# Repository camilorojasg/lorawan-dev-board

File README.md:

# lorawan-dev-board
Schematics and documentation of my Arduino LoRaWAN development board

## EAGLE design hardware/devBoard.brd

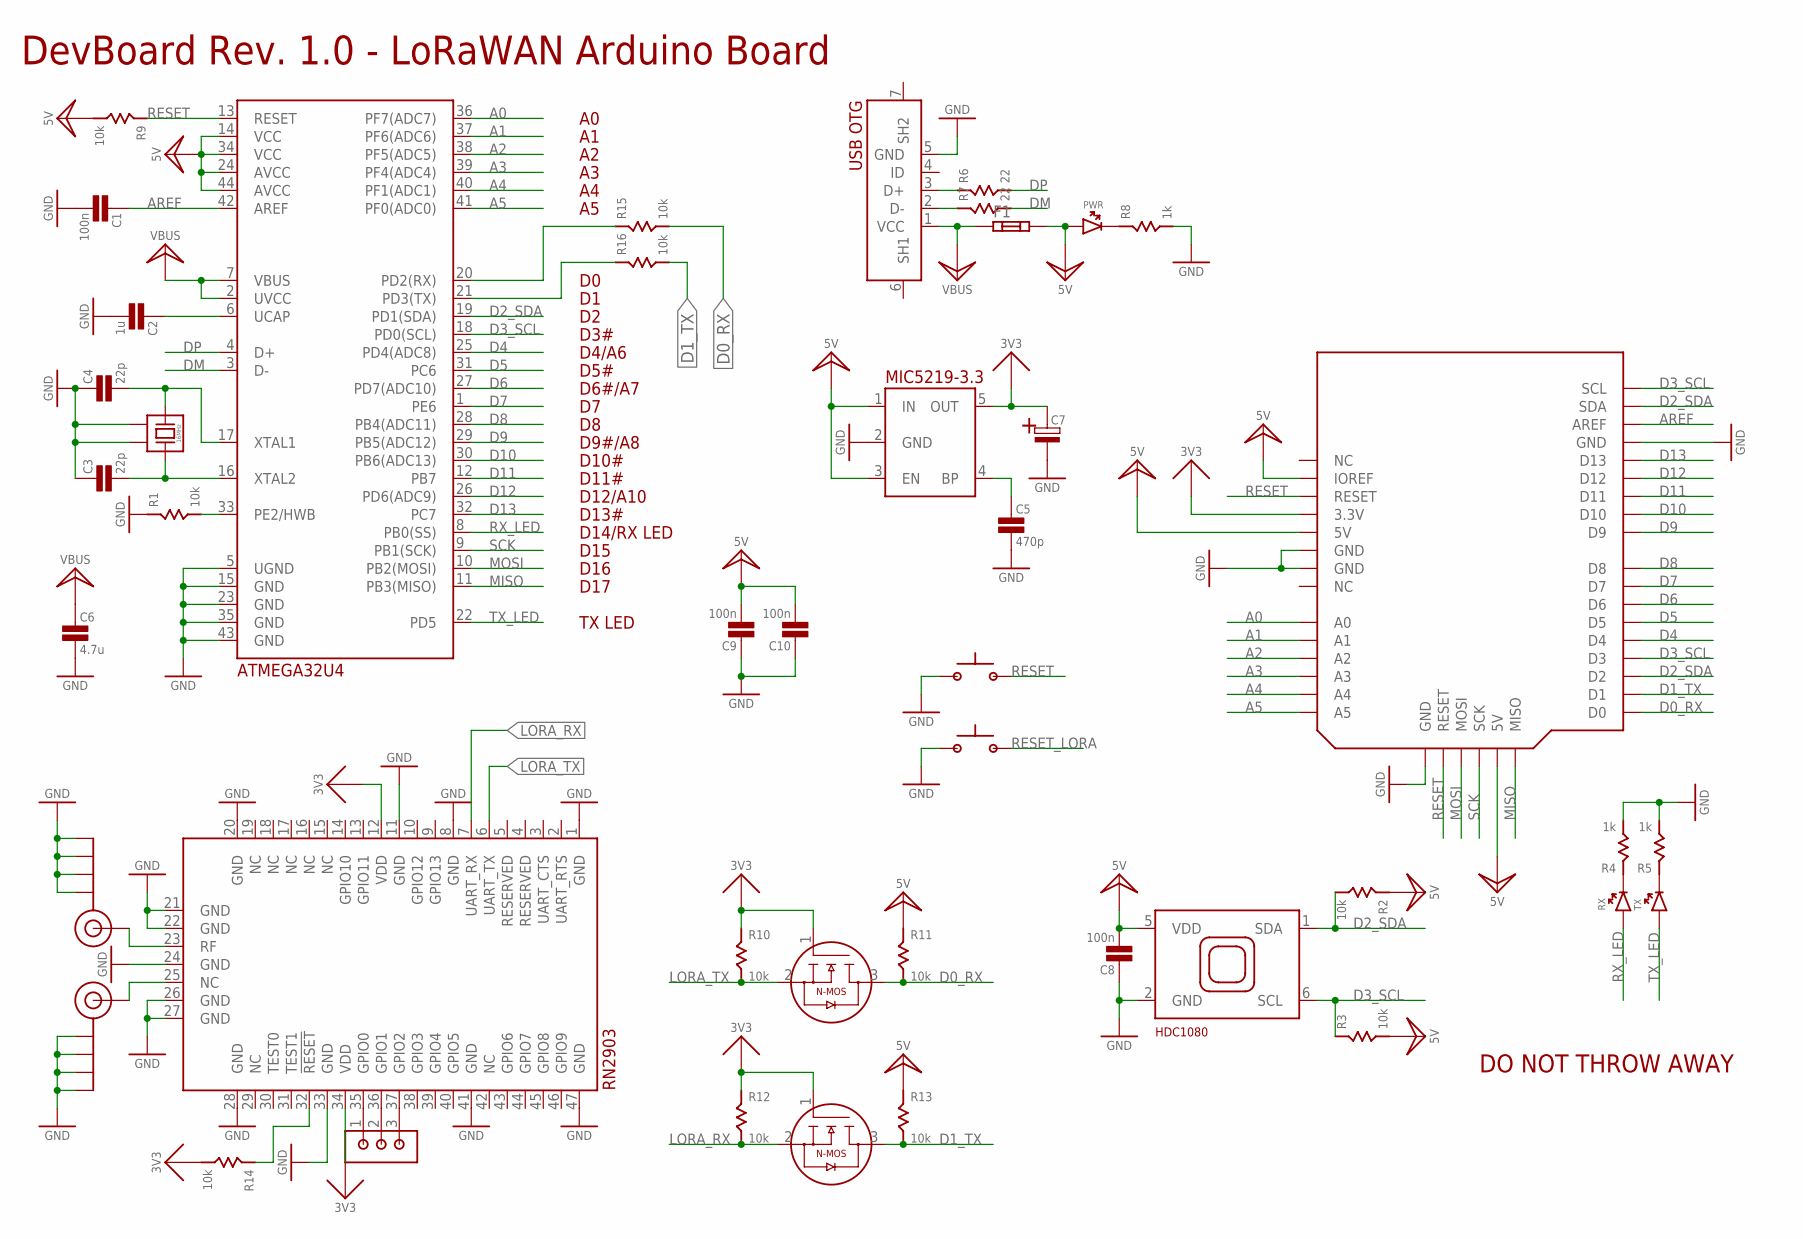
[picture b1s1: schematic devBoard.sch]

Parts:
C1, C8, C9, C10: 100n; 0603
C2: 1u; 0603
C3, C4: 22p; 0603
C5: 470p; 0603
C6: 4.7u; 0603
C7: CT3216
F1: MF-MSMF050
J$1, J$2: SMA_EDGE; SMA-EDGE
PWR: PWR; 0603LED
R1, R2, R3, R9, R10, R11, R12, R13, R14, R15, R16: 10k; 0603
R4, R5, R8: 1k; 0603
R6, R7: 22; 0603
RX: RX; 0603LED
SW2, SW3: PUSH_BTN
T1, T2: BSS138; SOT23-3
TX: TX; 0603LED
U1: RN2903
U$1: ATMEGA32U4-MU; QFN44
U$2: ARDUINO_UNO
U$9: HDC1080
U$34: MIC5219-3.3; SOT-23-5
U$45: USB_OTG
U$59: 1X3_HEADER
U$65: DONT_THROW
Y1: 16MHz; XTAL3225

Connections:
3V3: C7.AN, R10.1, R12.1, R14.2, T1.1 (G), T2.1 (G), U1.12 (VDD), U1.34 (VDD), U$2.3.3V, U$34.5 (OUT)
5V: C8.2, C9.2, C10.2, F1.2, PWR.AN, R2.1, R3.2, R9.2, R11.1, R13.1, U$1.14 (VCC), U$1.24 (AVCC), U$1.34 (VCC), U$1.44 (AVCC), U$2.5V, U$2.ICSP_2 (5V), U$2.IOREF, U$9.5 (VDD), U$34.1 (IN), U$34.3 (EN)
A0: U$1.36 (PF7(ADC7)), U$2.A0
A1: U$1.37 (PF6(ADC6)), U$2.A1
A2: U$1.38 (PF5(ADC5)), U$2.A2
A3: U$1.39 (PF4(ADC4)), U$2.A3
A4: U$1.40 (PF1(ADC1)), U$2.A4
A5: U$1.41 (PF0(ADC0)), U$2.A5
AREF: C1.1, U$1.42 (AREF), U$2.AREF
D0_RX: R11.2, R15.2, T1.3 (D), U$2.D0
D1_TX: R13.2, R16.2, T2.3 (D), U$2.D1
D2_SDA: R2.2, U$1.19 (PD1(SDA)), U$2.D2, U$2.SDA, U$9.1 (SDA)
D3_SCL: R3.1, U$1.18 (PD0(SCL)), U$2.D3, U$2.SCL, U$9.6 (SCL)
D4: U$1.25 (PD4(ADC8)), U$2.D4
D5: U$1.31 (PC6), U$2.D5
D6: U$1.27 (PD7(ADC10)), U$2.D6
D7: U$1.1 (PE6), U$2.D7
D8: U$1.28 (PB4(ADC11)), U$2.D8
D9: U$1.29 (PB5(ADC12)), U$2.D9
D10: U$1.30 (PB6(ADC13)), U$2.D10
D11: U$1.12 (PB7), U$2.D11
D12: U$1.26 (PD6(ADC9)), U$2.D12
D13: U$1.32 (PC7), U$2.D13
DM: R7.2, U$1.3 (D-)
DP: R6.2, U$1.4 (D+)
GND: C1.2, C2.2, C3.1, C4.1, C5.2, C6.2, C7.CAT, C8.1, C9.1, C10.1, J$1.GND@0 (GND), J$1.GND@1 (GND), J$1.GND@2 (GND), J$1.GND@3 (GND), J$2.GND@0 (GND), J$2.GND@1 (GND), J$2.GND@2 (GND), J$2.GND@3 (GND), R1.1, R4.2, R5.2, R8.2, SW2.1, SW3.1, U1.1 (GND), U1.8 (GND), U1.11 (GND), U1.20 (GND), U1.21 (GND), U1.22 (GND), U1.24 (GND), U1.26 (GND), U1.27 (GND), U1.28 (GND), U1.33 (GND), U1.41 (GND), U1.47 (GND), U$1.5 (UGND), U$1.15 (GND), U$1.23 (GND), U$1.35 (GND), U$1.43 (GND), U$2.GND@2 (GND), U$2.GND@3 (GND), U$2.GND@4 (GND), U$2.ICSP_6 (GND), U$9.2 (GND), U$34.2 (GND), U$45.5 (GND), Y1.2, Y1.4
LORA_RX: R12.2, T2.2 (S), U1.7 (UART_RX)
LORA_TX: R10.2, T1.2 (S), U1.6 (UART_TX)
MISO: U$1.11 (PB3(MISO)), U$2.ICSP_1 (MISO)
MOSI: U$1.10 (PB2(MOSI)), U$2.ICSP_4 (MOSI)
unnamed: R1.2, U$1.33 (PE2/HWB)
unnamed: C2.1, U$1.6 (UCAP)
unnamed: J$1.SIG (SIGNAL), U1.23 (RF)
unnamed: J$2.SIG (SIGNAL), U1.25 (NC)
unnamed: C3.2, U$1.16 (XTAL2), Y1.1
unnamed: C4.2, U$1.17 (XTAL1), Y1.3
unnamed: C5.1, U$34.4 (BP)
unnamed: R4.1, RX.CA
unnamed: R5.1, TX.CA
unnamed: R6.1, U$45.3 (D+)
unnamed: R7.1, U$45.2 (D-)
unnamed: PWR.CA, R8.1
unnamed: U1.37 (GPIO2), U$59.3
unnamed: U1.36 (GPIO1), U$59.2
unnamed: U1.35 (GPIO0), U$59.1
unnamed: R15.1, U$1.20 (PD2(RX))
unnamed: R16.1, U$1.21 (PD3(TX))
RESET: R9.1, SW2.2, U$1.13 (RESET), U$2.ICSP_5 (RESET), U$2.RESET
RESET_LORA: R14.1, SW3.2, U1.32 (!RESET)
RX_LED: RX.AN, U$1.8 (PB0(SS))
SCK: U$1.9 (PB1(SCK)), U$2.ICSP_3 (SCK)
TX_LED: TX.AN, U$1.22 (PD5)
VBUS: C6.1, F1.1, U$1.2 (UVCC), U$1.7 (VBUS), U$45.1 (VCC)

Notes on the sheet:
DevBoard Rev. 1.0 - LoRaWAN Arduino Board

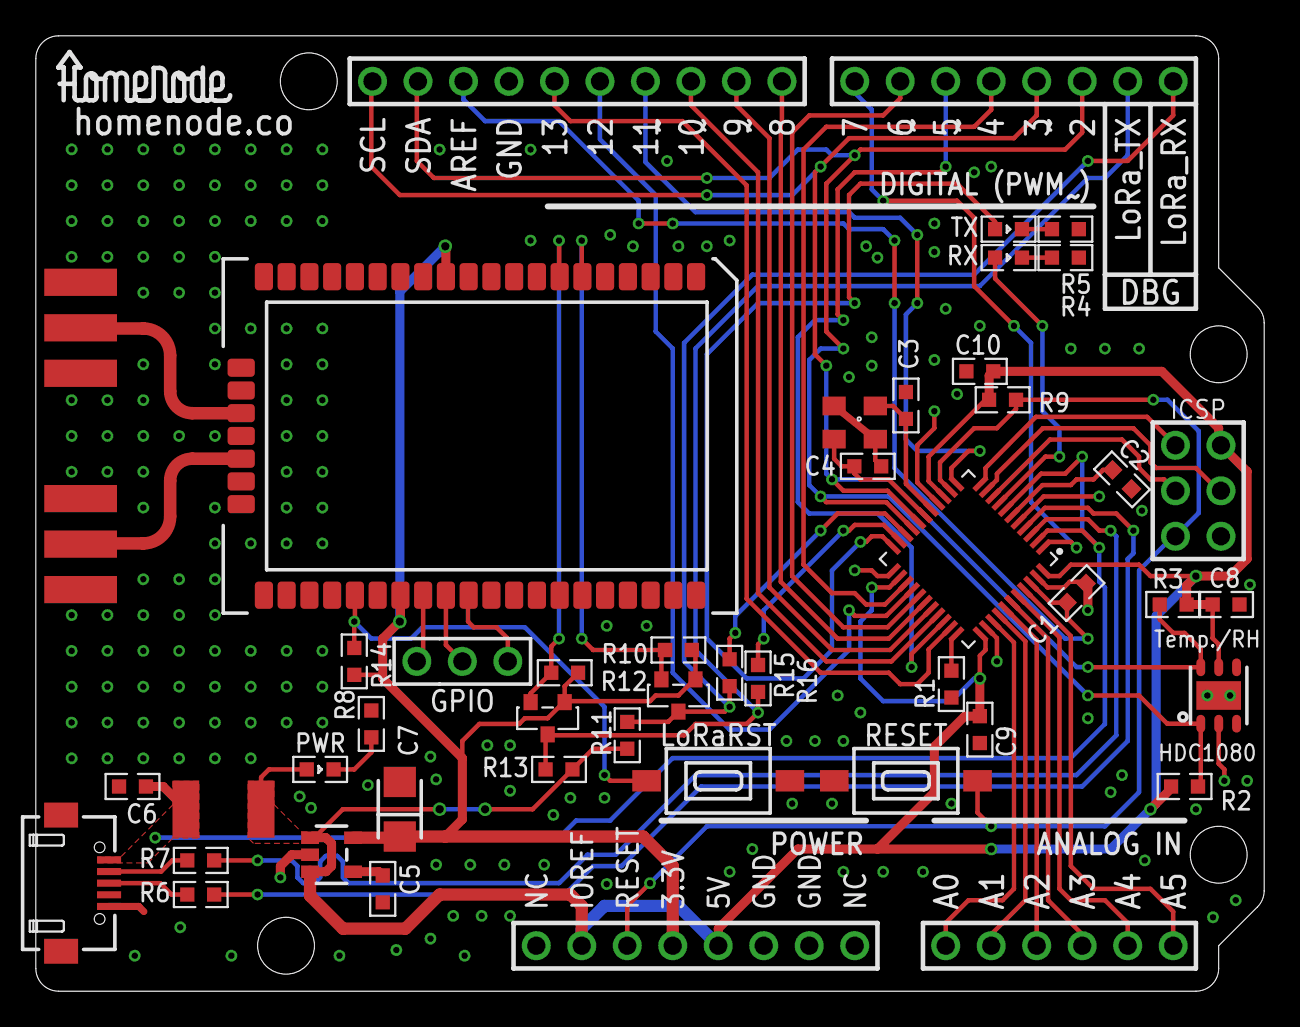
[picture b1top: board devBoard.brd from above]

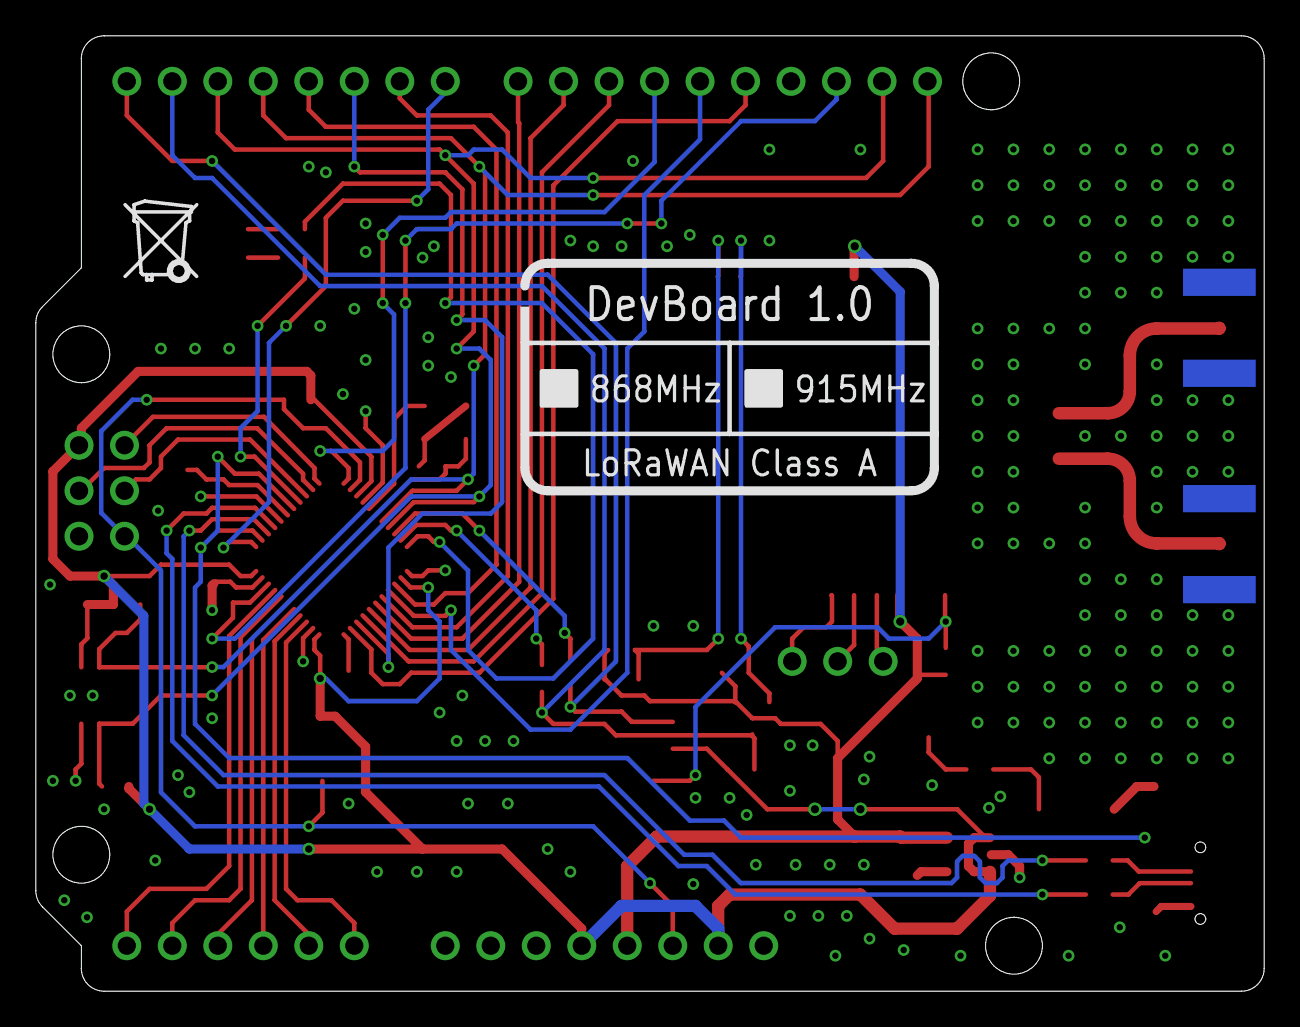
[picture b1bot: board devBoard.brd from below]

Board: 2 copper layers, 68.6 x 53.3 mm, 47 parts (2 on the bottom side), 53 nets.

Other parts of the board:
U$62: HOMENODE
U$63: BACK_LABEL

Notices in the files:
parts and their libraries:
SparkFun-Connectors: Licensing: Creative Commons ShareAlike 4.0 International - https://creativecommons.org/licenses/by-sa/4.0
